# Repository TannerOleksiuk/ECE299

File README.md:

# ECE299
Alarm Clock Design Project

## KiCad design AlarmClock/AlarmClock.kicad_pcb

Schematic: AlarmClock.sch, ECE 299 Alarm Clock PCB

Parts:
C1: 0.05uF; CAP.1
C2: 470uF; CAP_Pol_D6.3xH11.5xP2.0mm
C3, C5: 1nF; CAP.1
C4: 10uF; CAP_Pol_D6.3xH11.5xP2.0mm
D1, D2: Diode; DO41
LS1: Speaker; SolderWirePad_2x_1mmDrill
POT1: 100kΩ; Potentiometer_Alps_RK09K_Horizontal
Q1, Q2, Q3, Q4, Q5: 2N3904; TO92
R1: 10Ω; RES.3
R2, R15: 20kΩ; RES.3
R3, R4, R5, R6, R14: 1kΩ; RES.3
R7, R8, R9, R10, R11, R12, R13: 120Ω; RES.3
R16: 200Ω; RES.3
STM1: STM32_F407; STM32_F4
SW1, SW2, SW3, SW4, SW5: SW_Push_Dual; SW_PUSH_6mm
U1: LM386; DIP8
U2: LTC-4727JR
U3: LM358; DIP8

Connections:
+5V: C4.1 (+), STM1.2-4 (5V), U1.6 (V+)
GND: C3.2, C4.2 (-), LS1.2, POT1.3, Q1.1 (E), Q2.1 (E), Q3.1 (E), Q4.1 (E), Q5.1 (E), R1.1, STM1.1-1 (GND), STM1.1-2 (GND), STM1.1-5 (GND), STM1.1-23 (GND), STM1.1-49 (GND), STM1.1-50 (GND), STM1.2-1 (GND), STM1.2-2 (GND), STM1.2-49 (GND), STM1.2-50 (GND), STM1.JP21 (GND), STM1.JP22 (GND), STM1.JP31 (GND), STM1.JP32 (GND), U1.2 (-), U1.4 (Gnd), U3.4 (V-)
unnamed: C1.1, C2.1 (+), R16.2
unnamed: C1.2, R1.2
unnamed: C2.2 (-), D1.A (Anode)
unnamed: C3.1, R15.1, U3.3 (+)
unnamed: C5.2, R2.1, R15.2
unnamed: D1.K (Cathode), LS1.1
unnamed: D2.K (Cathode), SW1.2, SW2.2, SW3.2, SW4.2, SW5.2
unnamed: POT1.2, U1.3 (+)
unnamed: Q1.2 (B), R3.1
unnamed: Q1.3 (C), U2.8 (D4)
unnamed: Q2.2 (B), R4.1
unnamed: Q2.3 (C), U2.6 (D3)
unnamed: Q3.2 (B), R5.1
unnamed: Q3.3 (C), U2.4 (L)
unnamed: Q4.2 (B), R6.1
unnamed: Q4.3 (C), U2.2 (D2)
unnamed: Q5.2 (B), R14.1
unnamed: Q5.3 (C), U2.1 (D1)
unnamed: R7.2, U2.14 (A,L1)
unnamed: R8.2, U2.16 (B,L2)
unnamed: R9.2, U2.13 (C,L3)
unnamed: R10.2, U2.3 (D)
unnamed: R11.2, U2.5 (E)
unnamed: R12.2, U2.11 (F)
unnamed: R13.2, U2.15 (G)
unnamed: R16.1, U1.5
PA4: R2.2, STM1.1-16 (PA4)
PC4: STM1.1-20 (PC4), SW1.1
PC5: STM1.1-19 (PC5), SW2.1
PC8: STM1.2-45 (PC8), SW3.1
PC9: STM1.2-46 (PC9), SW4.1
PC11: STM1.2-38 (PC11), SW5.1
PD4: R14.2, STM1.2-32 (PD4)
PD7: R6.2, STM1.2-27 (PD7)
PD8: R5.2, STM1.1-40 (PD8)
PD9: R3.2, STM1.1-41 (PD9)
PD10: R4.2, STM1.1-42 (PD10)
PD11: STM1.1-43 (PD11)
PE6: STM1.2-11 (PE6)
PE7: R7.1, STM1.1-25 (PE7)
PE8: R8.1, STM1.1-26 (PE8)
PE9: R9.1, STM1.1-27 (PE9)
PE10: R10.1, STM1.1-28 (PE10)
PE11: R11.1, STM1.1-29 (PE11)
PE12: R12.1, STM1.1-30 (PE12)
PE13: R13.1, STM1.1-31 (PE13)
PE14: STM1.1-32 (PE14)
PE15: STM1.1-33 (PE15)
Vf: C5.1, POT1.1, U3.1, U3.2 (-)

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
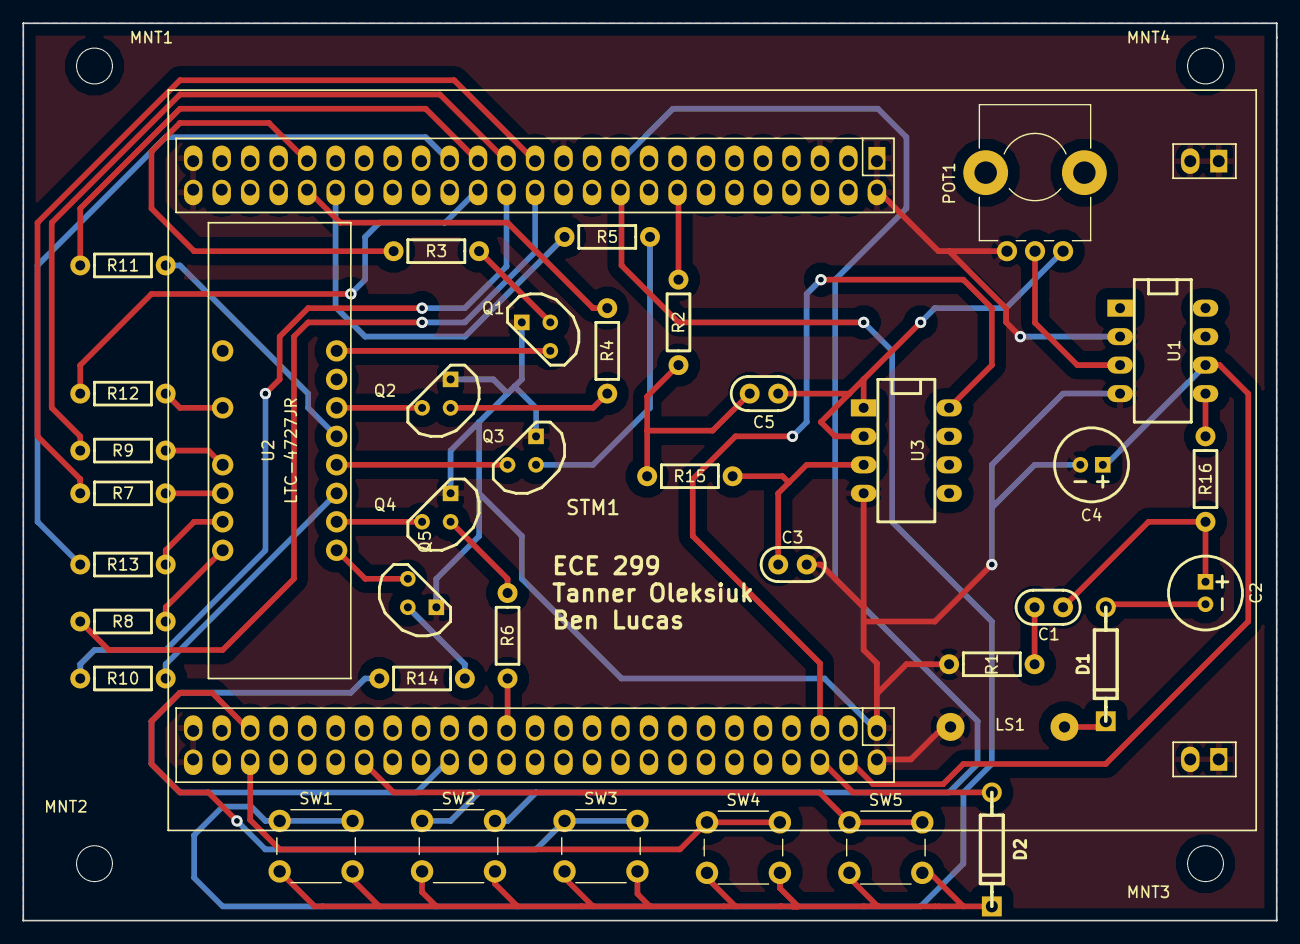
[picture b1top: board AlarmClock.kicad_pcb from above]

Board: 2 copper layers, 111.8 x 80.0 mm, 43 parts (0 on the bottom side), 48 nets.

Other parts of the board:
MNT1, MNT2, MNT3, MNT4: MountingHole_3.2mm_M3

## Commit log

2018-06-15 KiCAD Files
2018-06-15 Added op amp circuit
2018-06-19 STM Board added to op amp schematic
2018-06-21 added labels to STM
2018-06-21 7 seg
2018-06-21 changed name of 7segment for clarity
2018-06-21 blah blah blah
2018-06-21 push button circuit added
2018-06-22 finalized for now...
    we should add circuit protection and stuff at some point but honestly its probably fine for assignment submission. Also added a cap between supply voltage and ground since as we saw in the lab, that 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
2018-06-29 fixed op amp circuit and 7-seg
2018-06-29 Modified schematic to include low pass filter and removed PB circuit
2018-06-29 final schem
2018-06-30 Added Footprints
    Added footprints to all components except 100kOhm potentiometer, also we need to add push buttons and figure out how they are going to work with the pull up/down resistors in the stm board
2018-07-03 added pushbuttons
2018-07-05 geber files and final pcb
2018-07-12 generated bom
2018-07-23 added test code
2018-07-31 added stuff, doesn't work but on right path
2018-07-31 works gud
2018-08-01 just a bit left
2018-08-01 Done :)
